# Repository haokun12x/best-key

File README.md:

# BK46 — 46 键正交 / 双直驱力反馈旋钮 / TMR + 机械轴共用 / 三模 / 无线充电

> **当前状态：外壳、主板、两块旋钮小板的制作文件齐全。三块板都已 100% 布通，KiCad DRC 零错误、零未连接（主板只剩 7 处元件占位框重叠的警告）。固件未写，电子部分整体未经打样验证，BOM 编号需核对。** 详见文末「完成度与待办」。

## 1. 方案总览

| 项目 | 方案 |
|---|---|
| 配列 | 4×12 正交网格，19.05 mm 间距；左上角、右上角两格换成旋钮，共 46 键 |
| 外形 | 237.2 × 84.8 × 19.8 mm（不含脚垫），四周只比键区多 4.3 mm，圆角 R4 |
| 轴体 | 每键同时有 Kailh 热插拔座（三脚/五脚机械轴）和一颗 SOT-23 线性磁传感器（磁轴） |
| 旋钮 | 2 个，1404 级无刷外转子电机直驱 + STSPIN233 驱动 + MT6701 磁编码器；带模拟量下压识别，咔哒与震动由电机模拟 |
| RGB | 每键一颗 WS2812B-2020，正面贴装在轴体灯位，整条灯带电源可关断 |
| 显示 | 0.91" 128×32 OLED（SSD1306，38×12 mm 成品模块），嵌在前壁中央 |
| 主控 | Raytac MDBT50Q-1MV2（nRF52840）：USB、蓝牙、2.4G（配 nRF52840 接收器） |
| 固件 | RMK（用 Vial 上位机改键/层/宏）或 ZMK；**不能刷 QMK / Vial-QMK**；预留 W25Q32 外置闪存。移植要点见 `docs/firmware.md` |
| 电源 | USB-C 或 Qi 5 V 接收模块 → BQ24075 充电与路径管理 → 304060 锂电（约 800 mAh）→ XC6206 3.3 V |
| 结构 | 底壳 + 上框两件式，定位板上下各 15 段 Poron 垫片夹持（gasket），底部 8 颗 M2×18 沉头螺丝 |
| 重量 | 尼龙打印外壳约 65 g（底壳 53 + 上框 12）；FR4 定位板约 24 g |

相对最初想法的改动：

- **旋钮**：真正的侧面表冠放不下任何现成直驱电机（除非凸出约 7 mm），最终按你的决定改为左右上角各一个立式旋钮。
- **下压**：不做有行程的按压机构（1u 空间里会晃）。电机座是小板上由 4 根 FR4 梁悬挂的小岛，按压时下沉几十微米，由背面轴心的磁传感器测出，输出模拟量，接到主板复用器空余的两路。没有采用 MT6701 自带的按钮功能，因为它需要零点几毫米的轴向行程。
- **显示屏**：按你的想法放在朝向用户的前壁。从上方看是斜视角，所以选了视角最宽的 OLED。
- **无线充电**：用成品 Qi 接收贴片（线圈 + 小板，输出 5 V），焊到主板 `QI5V`/`GND` 两个焊盘，不自己设计接收电路。

## 2. 叠层（Z 向，单位 mm，从底面算起）

图：`mech/out/drawings/00_stackup_section.svg`

| 高度 | 内容 |
|---|---|
| 0 – 1.6 | 底壳底板 |
| 1.6 – 7.2 | 腔体 5.6：电池 3.2、Qi 线圈约 1.3、热插拔座向下 1.85；旋钮小板 0.6 厚，垫高 0.4（2.0 – 2.6） |
| 7.2 – 8.8 | 主板 1.6（4 层） |
| 8.8 – 12.3 | 轴体下壳 / 夹心棉 3.5 |
| 11.1 | 底壳垫片台顶面 |
| 12.3 – 13.8 | 定位板 1.5（FR4 / PC / 铝均可） |
| 15.0 | 底壳与上框分界面，上框压边底面 |
| 15.0 – 19.8 | 上框 |
| 3.8 – 17.3 | 电机（座在 0.6 小板 + 1.2 垫片上） |
| 17.6 – 31.0 | 旋钮帽，直径 18.6 |

垫片：1.5 mm 厚 Poron 条，宽 1.5 mm，贴在定位板边缘正反两面，压缩到 1.2 mm。位置见 `05_gasket_positions_x2.dxf`。

## 3. 文件清单

```
index.html                  项目主页（逐层拆解展示，可直接用 GitHub Pages 从仓库根目录发布）
site/render/, render_previews.py   主页用的外壳线稿及生成脚本
mech/params.py              所有机械尺寸的唯一来源
mech/build_case.py          外壳 CAD 脚本（CadQuery），含干涉检查
mech/build_drawings.py      各层 DXF 图纸与叠层剖面图
mech/out/*.step, *.stl      底壳 tub、上框 bezel、定位板 plate、旋钮帽 knob_cap、旋钮芯 knob_core、电机垫片 motor_spacer
mech/out/bk46_assembly.step 总装（含 PCB、电池、线圈、电机、键帽包络等参考体）
mech/out/drawings/          00 叠层剖面  01 定位板  02 上框  03/04 底壳剖面与底孔  05 垫片位置  06 夹心棉  07 腔内布局
pcb/main/bk46_main.kicad_pcb / .kicad_pro   主板（4 层 1.6 mm）
pcb/main/unconnected.txt    主板连通状态（现为全部连通）
pcb/main/fab/               主板 Gerber、钻孔、贴片坐标、四层铜 SVG
pcb/main/bom_main.csv, keymap.json, netlist.json, drc.json
pcb/knob/L, pcb/knob/R      左、右旋钮小板（2 层 0.6 mm），各含 KiCad 工程和 fab/ 制板文件
pcb/knob/bom_knob.csv, ffc_pinmap.json
pcb/gen_main.py, gen_knob.py, router.py   板子的生成脚本和自写布线器
docs/firmware.md            固件移植说明：扫描、力反馈效果、下压识别、引脚
analysis/tmr_field.py, .svg 磁轴磁场仿真
tools/                      kpy.sh（KiCad 自带 Python）、drc.sh、freeroute.py（调用 Freerouting）、write_pro.py、sympins.py、
                            patch_route.py（拆线重布补线器）、clean_dangling.py（清悬空线）、finish_main.sh（主板收尾流程）
```

重新生成（主板约 2 分钟）：

```bash
.venv/bin/python mech/build_case.py
```
```bash
tools/kpy.sh pcb/gen_main.py
```
生成器自身会剩几处连不上的线，再用收尾流程补完（约 35 分钟，结果写到 `pcb/main_fin/`，确认后复制回 `pcb/main/`）：
```bash
tools/finish_main.sh pcb/main/bk46_main.kicad_pcb pcb/main_fin
```
```bash
tools/kpy.sh pcb/gen_knob.py
```
```bash
tools/kpy.sh tools/freeroute.py pcb/knob/L/bk46_knob_L_unrouted.kicad_pcb pcb/knob/L/bk46_knob_L.kicad_pcb 200 --zones=GND:F.Cu,GND:B.Cu
```

## 4. 电路架构

### 4.1 按键扫描（机械轴、磁轴、旋钮下压共用一条链路）

- 每键：传感器 OUT →10 kΩ→ `KEY` 节点 → CD74HC4067 的一路输入；热插拔座一脚接 `KEY`，另一脚接地。
- 装磁轴时 `KEY` 跟随传感器输出，读到模拟行程；装机械轴时按下把 `KEY` 拉到 0 V。固件校准时自动判定每个键是哪种轴。
- 没有二极管矩阵，天然全键无冲。3 颗 16 选 1 复用器共 48 路：46 个键 + 2 个旋钮下压。
- 传感器电源由 P-MOS 开关控制，空闲时低频间歇上电。
- 第 1、3 行轴体旋转 180°，使 PCB 前缘、后缘和中间各空出一条没有热插拔座的带状区域放元件。

### 4.2 主控引脚

| 功能 | 引脚 | 功能 | 引脚 |
|---|---|---|---|
| MUXA / MUXB / MUXC（ADC） | P0.29 / P0.31 / P0.30 | 电池电压 | P0.04 |
| 复用器 S0–S3 | P0.27, P0.06, P0.08, P1.09 | 传感器电源使能（低有效） | P1.12 |
| 左旋钮三相 PWM | P1.10, P1.11, P1.13 | 右旋钮三相 PWM | P0.13, P0.15, P0.17 |
| 编码器 CLK / DO（共用） | P0.22 / P0.24 | 编码器片选 左 / 右 | P1.15 / P0.20 |
| 旋钮电源使能（低有效） | P0.19 | 充电状态 | P0.03 |
| LED 数据 | P0.23 | LED 电源使能（高有效） | P1.14 |
| OLED SDA / SCL | P0.14 / P0.16 | 复位 | P0.18 |
| 外置闪存 CS / CLK / MOSI / MISO | P0.02 / P0.28 / P0.26 / P0.05 | | |

每个键的复用器通道和 LED 序号在 `pcb/main/keymap.json`。旋钮下压：左 = 复用器 A 通道 0，右 = 复用器 C 通道 15。

### 4.3 旋钮模块

- **小板**：0.6 mm 双层板。电机座是 13 mm 见方的小岛，四边各由一座 3 mm 宽的桥连到 2 mm 宽的 FR4 梁上，梁两端在四角用螺丝固定在底壳凸台上。估算刚度约 190 N/mm，4 N 按压下沉约 0.02 mm，未实测。
- **角度**：MT6701QT 在小岛正面轴心，对着粘在电机轴底的径向磁铁。
- **下压**：Z 向线性磁传感器（SOT-23）在小岛背面轴心，对着粘在底壳孔里的 Ø3×0.5 磁铁。
- **驱动**：STSPIN233 在小板尾部；使能脚固定上拉到旋钮电源，整路由主板的 P-MOS 开关控制。
- **排线**：14P 0.5 mm 同向 FFC，约 30 mm。主板连接器朝后壁出线，排线向下折 180° 插入正下方的小板连接器。引脚自西向东（左旋钮）：`VSYS ×3, GND ×3, K3V3, U, V, W, PRESS, CSN, CLK, DO`；右旋钮镜像。
- 电机三相线焊在小板的 M1–M3 焊盘。
- 力反馈效果、下压算法和低功耗策略见 `docs/firmware.md`。

## 5. 外购件

| 件 | 规格 | 数量 |
|---|---|---|
| 电机 | 1404 级无刷外转子，机身 ≤ Ø18.9 × 13.5，底部 4×M2（9×9 mm），T 型桨座（2×M2 间距 5 mm） | 2 |
| 径向充磁磁铁 | Ø4×2，粘在电机轴底端 | 2 |
| 轴向充磁磁铁 | Ø3×0.5，粘在底壳电机轴心孔内，与底面齐平 | 2 |
| OLED | 0.91" SSD1306 I2C 模块，PCB 38×12 | 1 |
| 电池 | 304060 锂聚合物，带保护板，JST-SH 2P（核对极性） | 1 |
| Qi 接收 | 5 V 成品接收贴片，线圈 ≤ 48×34 | 1 |
| FFC | 14P 0.5 mm 同向，30 mm | 2 |
| 螺丝 | M2×18 沉头（上框）×8；M2×4 盘头（电机，从小板背面拧入）×8；M2×3 自攻（小板固定）×10；M2×3（定位板铜柱）×20；M2×4（旋钮帽芯）×4 | |
| 铜柱 | M2×3.5 双通 | 10 |
| 垫片 | 1.5 mm Poron，裁 1.5 mm 宽 | 30 段 |
| 接收器 | nRF52840 USB Dongle（2.4G 模式用） | 1 |

主板元件见 `pcb/main/bom_main.csv`，小板见 `pcb/knob/bom_knob.csv`。立创编号是凭记忆填的，下单前必须逐个核对。

## 6. 装配顺序

1. 旋钮模块：电机垫片夹在小板和电机之间，4 颗 M2×4 从小板背面拧进电机底座；径向磁铁粘在轴底。
2. Ø3×0.5 磁铁粘进底壳轴心孔。把旋钮模块放到底壳凸台上，四角 4 颗、尾部 1 颗自攻螺丝固定。电机螺丝头落在底壳的让位孔里，不能碰到孔壁。
3. OLED 模块从上方滑入前壁口袋固定；电池、Qi 线圈贴在底板上（位置见 `07_floor_layout.dxf`）。
4. 主板与定位板用 10 根 3.5 mm 铜柱连接，装轴，定位板边缘正反贴垫片。
5. 接好两条排线、电池、Qi、OLED 四根线，USB 一端先斜插进后壁开口，再放平。
6. 盖上框，从底面拧 8 颗 M2×18。尼龙上框用自攻方式（底孔 Ø1.7），铝上框攻 M2 牙。
7. 旋钮芯用 2 颗 M2 拧在电机转子上，压上旋钮帽。

维修时拆 8 颗底部螺丝，上框可带着键帽直接提起，内胆随后取出。

## 7. 完成度与待办

### 已验证

- 外壳各零件与 PCB、电机、电池、线圈、显示模块、键帽包络之间的干涉检查全部为 0。
- 左、右旋钮小板：100% 布通，KiCad DRC 零违规、零未连接。
- 主板：100% 布通，KiCad DRC 零错误、零未连接、零悬空线、零孔距问题（间距规则 0.10 mm，最细线 0.15 mm，过孔 0.45/0.20 mm，属 4 层板常规工艺）。剩 7 处元件占位框重叠警告（两个 FFC 座与旁边阻容、C1/C2、C3 与 J1/U138），焊盘之间不冲突，贴片前看一眼即可。
- 所有 IC 的引脚定义取自 KiCad 官方符号库。

### 主板收尾时做的取舍

- 主控模块内圈焊盘之间只容得下 0.15 mm 线，所以补线统一用 0.15 mm；电源网络（VSYS、VBUS、VBAT、K3V3、VSENSE）重布时保持原线宽，VSYS 仍为 0.5 mm。
- 部分 +3V3 走线由 0.25 mm 换成了 0.15 mm（总电流约 0.2 A 以内，压降估计 30 mV 量级）。
- `CHG`、`SWDIO` 和一小段 +3V3 共约 13 mm 走在 In1 地平面上，地平面上因此有几条短缝，对这块板的信号影响很小。
- 删掉了 15 个与其他孔重叠或间距不足的 GND/VLED 过孔（地和 LED 电源有整层平面，连通性已由 DRC 复核）。

### 未完成

1. 没有原理图，网表以生成脚本和 `netlist.json` 为准。
2. 固件未写；`docs/firmware.md` 是移植说明，不是代码。
3. BOM 里的立创编号凭记忆填写，下单前逐个核对。

### 需要打样验证的风险

1. **按键传感器选型（最重要）**。传感器在轴心南侧 3.5 mm。`analysis/tmr_field.py` 的仿真结果：

   | 传感方式 | 释放 → 触底场强 | 是否单调 | 触底前 0.5 mm 的斜率 |
   |---|---|---|---|
   | 轴心正下方 Z 向（纯磁轴板的做法） | 9.6 → 58 mT | 是 | 33 mT/mm |
   | 偏 3.5 mm，Z 向（如 TMR2617S） | 5.4 → 10.3 mT | 否 | 0.4 mT/mm |
   | 偏 3.5 mm，面内径向 | 4.1 → 19.5 mT | 是 | 8.1 mT/mm |

   应选**面内感应**的线性 TMR，敏感轴指向轴心。BOM 里暂填的 TMR2617S 是 Z 向的，在这个位置触底前约 0.7 mm 分辨不出行程。我没能确认具体的面内型号，磁铁尺寸也是假设值，建议先做 2×2 小板验证；若所选传感器敏感轴方向不同，封装要转 90°。
2. **旋钮下压灵敏度**。梁的刚度和磁场梯度都是估算，按 4 N 约 1 mT 的信号量级设计；实际偏小可把小板换成 0.4 mm 或把梁铣窄，偏大则加厚。电机磁钢对下压传感器的串扰未评估。
3. **MT6701 的 MODE 脚**按"接地 = SSI/I2C"连接，需对照手册确认。
4. **力反馈强度**约 5 mN·m 是按电机参数估算的。电机相电阻很低，固件必须限流。
5. **左旋钮 PWM 用了 P1.10/P1.11/P1.13**，属于芯片的低频引脚，出力时可能影响蓝牙灵敏度。
6. **电机尺寸**因品牌而异，`params.py` 里 `MOTOR_*` 要按实物改。
7. **RGB 供电**直接用电池电压，电量低时蓝绿光偏暗；固件要限制总电流。
8. **无线充电**的交变磁场和带磁吸的充电座会干扰磁传感器。
9. **天线**在板子中部，周围是铺铜和金属轴座，蓝牙距离会打折扣。
10. **显示模块**的显示区偏移因厂家而异，`DISP_WIN_DX` 要按实物量。
11. **正贴 2020 灯珠**能否放进轴体灯槽取决于轴体，放不下可换 1.5×1.5 的 SK6805-EC15。
12. 0.6 mm 的旋钮小板较软，贴片时需要托板。

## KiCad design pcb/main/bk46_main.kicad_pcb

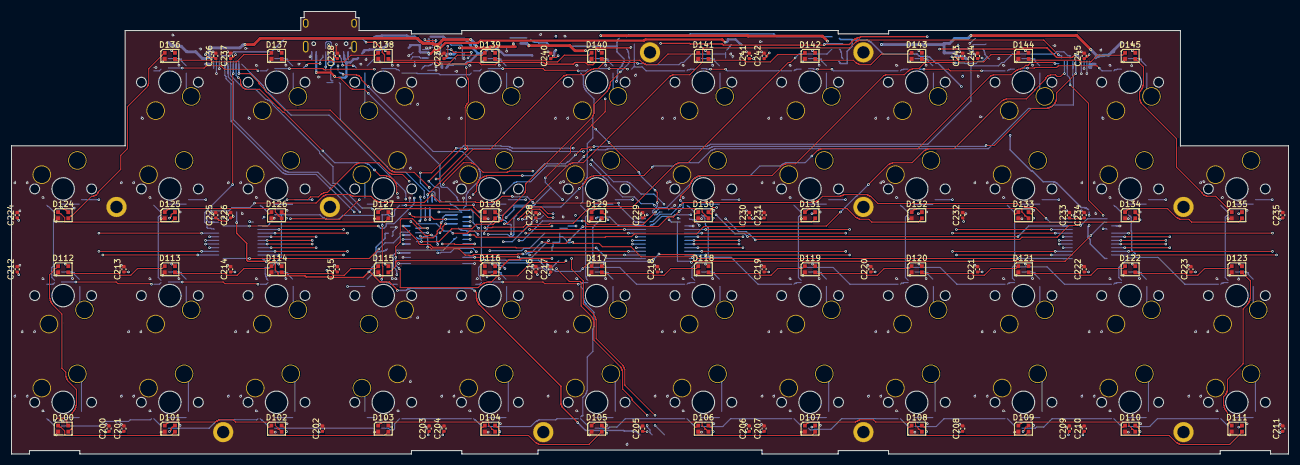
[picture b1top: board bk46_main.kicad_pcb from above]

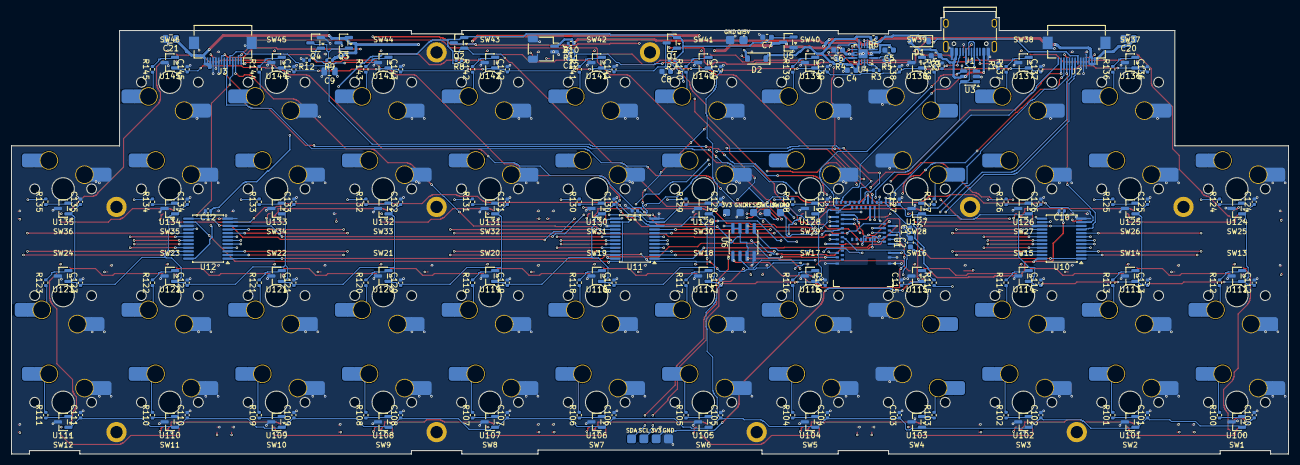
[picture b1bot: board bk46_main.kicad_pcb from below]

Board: 4 copper layers, 228.0 x 79.0 mm, 341 parts (183 on the bottom side), 190 nets.

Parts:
C1, C10, C11, C12, C12#2, C200, C201, C202, C203, C204, C205, C206, C207, C208, C209, C210, C211, C212, C213, C214, C215, C216, C217, C218, C219, C220, C221, C222, C223, C224, C225, C226, C228, C229, C230, C231, C232, C233, C234, C235, C236, C237, C238, C239, C240, C241, C242, C243, C244, C245: 100n; C_0402_1005Metric
C2, C3, C5, C6: 4u7; C_0603_1608Metric
C4, C7, C8: 1u; C_0603_1608Metric
C9: 10u; C_0805_2012Metric
C20, C21: 22u; C_0805_2012Metric
C100, C101, C102, C103, C104, C105, C106, C107, C108, C109, C110, C111, C112, C113, C114, C115, C116, C117, C118, C119, C120, C121, C122, C123, C124, C125, C126, C127, C128, C129, C130, C131, C132, C133, C134, C135, C136, C137, C138, C139, C140, C141, C142, C143, C144, C145: 22n; C_0402_1005Metric
D1, D2: B5819W; D_SOD-123
D100, D101, D102, D103, D104, D105, D106, D107, D108, D109, D110, D111, D112, D113, D114, D115, D116, D117, D118, D119, D120, D121, D122, D123, D124, D125, D126, D127, D128, D129, D130, D131, D132, D133, D134, D135, D136, D137, D138, D139, D140, D141, D142, D143, D144, D145: WS2812B-2020; LED_WS2812B-2020_PLCC4_2.0x2.0mm
H1, H2, H3, H4, H5, H6, H7, H8, H9, H10: M2 standoff 3.5mm
J1: USB-C 16P; USB_C_Receptacle_HRO_TYPE-C-31-M-12
J2, J3: FFC 14P 0.5mm; Hirose_FH12-14S-0.5SH_1x14-1MP_P0.50mm_Horizontal
J4: BAT (JST-SH 2P); JST_SH_SM02B-SRSS-TB_1x02-1MP_P1.00mm_Horizontal
Q1, Q2, Q3: AO3401A; SOT-23
Q4: 2N7002; SOT-23
R1, R2: 5k1; R_0402_1005Metric
R3: 2k2; R_0402_1005Metric
R4: 1k5; R_0402_1005Metric
R5, R6, R100, R101, R102, R103, R104, R105, R106, R107, R108, R109, R110, R111, R112, R113, R114, R115, R116, R117, R118, R119, R120, R121, R122, R123, R124, R125, R126, R127, R128, R129, R130, R131, R132, R133, R134, R135, R136, R137, R138, R139, R140, R141, R142, R143, R144, R145: 10k; R_0402_1005Metric
R7, R8, R9, R12: 100k; R_0402_1005Metric
R10, R11: 1M; R_0402_1005Metric
SW1, SW2, SW3, SW4, SW5, SW6, SW7, SW8, SW9, SW10, SW11, SW12, SW13, SW14, SW15, SW16, SW17, SW18, SW19, SW20, SW21, SW22, SW23, SW24, SW25, SW26, SW27, SW28, SW29, SW30, SW31, SW32, SW33, SW34, SW35, SW36, SW37, SW38, SW39, SW40, SW41, SW42, SW43, SW44, SW45, SW46: MX_HS_TMR
TP1: QI5V
TP2, TP10, TP23: GND
TP11, TP24: +3V3
TP12: SCL
TP13: SDA
TP20: SWDIO
TP21: SWCLK
TP22: RESET
U1: MDBT50Q-1MV2; Raytac_MDBT50Q
U3: USBLC6-2SC6; SOT-23-6
U4: BQ24075RGT; VQFN-16-1EP_3x3mm_P0.5mm_EP1.6x1.6mm
U5: XC6206P332MR; SOT-23
U6: W25Q32JVSSIQ (optional); SOIC-8_3.9x4.9mm_P1.27mm
U10, U11, U12: CD74HC4067SM96; SSOP-24_5.3x8.2mm_P0.65mm
U100, U101, U102, U103, U104, U105, U106, U107, U108, U109, U110, U111, U112, U113, U114, U115, U116, U117, U118, U119, U120, U121, U122, U123, U124, U125, U126, U127, U128, U129, U130, U131, U132, U133, U134, U135, U136, U137, U138, U139, U140, U141, U142, U143, U144, U145: TMR2617S; SOT-23

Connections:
+3V3: C1.1, C2.1, C7.1, C10.1, C11.1, C12#2.1, Q1.2, Q2.2, R7.1, R8.1, TP11.1, TP24.1, U1.28, U1.30, U5.2, U6.3, U6.7, U6.8, U10.24, U11.24, U12.24
CC1: J1.A5, R1.1
CC2: J1.B5, R2.1
CHG: U1.9, U4.9
EN1: R6.1, U4.6
ENC_CLK: J2.13, J3.2, U1.46
ENC_CSN1: J2.12, U1.8
ENC_CSN2: J3.3, U1.44
ENC_DO: J2.14, J3.1, U1.48
FL_CLK: U1.13, U6.6
FL_CS: U1.11, U6.1
FL_MISO: U1.21, U6.2
FL_MOSI: U1.19, U6.5
GND: C1.2, C2.2, C3.2, C4.2, C5.2, C6.2, C7.2, C8.2, C9.2, C10.2, C11.2, C12.2, C12#2.2, C20.2, C21.2, C100.2, C101.2, C102.2, C103.2, C104.2, C105.2, C106.2, C107.2, C108.2, C109.2, C110.2, C111.2, C112.2, C113.2, C114.2, C115.2, C116.2, C117.2, C118.2, C119.2, C120.2, C121.2, C122.2, C123.2, C124.2, C125.2, C126.2, C127.2, C128.2, C129.2, C130.2, C131.2, C132.2, C133.2, C134.2, C135.2, C136.2, C137.2, C138.2, C139.2, C140.2, C141.2, C142.2, C143.2, C144.2, C145.2, C200.2, C201.2, C202.2, C203.2, C204.2, C205.2, C206.2, C207.2, C208.2, C209.2, C210.2, C211.2, C212.2, C213.2, C214.2, C215.2, C216.2, C217.2, C218.2, C219.2, C220.2, C221.2, C222.2, C223.2, C224.2, C225.2, C226.2, C228.2, C229.2, C230.2, C231.2, C232.2, C233.2, C234.2, C235.2, C236.2, C237.2, C238.2, C239.2, C240.2, C241.2, C242.2, C243.2, C244.2, C245.2, D100.2, D101.2, D102.2, D103.2, D104.2, D105.2, D106.2, D107.2, D108.2, D109.2, D110.2, D111.2, D112.2, D113.2, D114.2, D115.2, D116.2, D117.2, D118.2, D119.2, D120.2, D121.2, D122.2, D123.2, D124.2, D125.2, D126.2, D127.2, D128.2, D129.2, D130.2, D131.2, D132.2, D133.2, D134.2, D135.2, D136.2, D137.2, D138.2, D139.2, D140.2, D141.2, D142.2, D143.2, D144.2, D145.2, H1.1, H2.1, H3.1, H4.1, H5.1, H6.1, H7.1, H8.1, H9.1, H10.1, J1.A1, J1.A12, J1.B1, J1.B12, J1.SH, J2.4, J2.5, J2.6, J2.MP, J3.9, J3.10, J3.11, J3.MP, J4.2, J4.MP, Q4.2, R1.2, R2.2, R3.2, R4.2, R5.2, R11.2, R12.2, SW1.1, SW2.1, SW3.1, SW4.2, SW5.1, SW6.1, SW7.1, SW8.1, SW9.1, SW10.1, SW11.1, SW12.1, SW13.2, SW14.2, SW15.2, SW16.1, SW17.2, SW18.2, SW19.2, SW20.2, SW21.2, SW22.2, SW23.2, SW24.2, SW25.1, SW26.1, SW27.1, SW28.2, SW29.1, SW30.1, SW31.1, SW32.1, SW33.1, SW34.1, SW35.1, SW36.1, SW37.2, SW38.2, SW39.1, SW40.2, SW41.2, SW42.2, SW43.2, SW44.2, SW45.2, SW46.2, TP2.1, TP10.1, TP23.1, U1.1, U1.2, U1.15, U1.33, U1.55, U3.2, U4.4, U4.5, U4.8, U4.15, U4.17, U5.1, U6.4, U10.12, U10.15, U11.12, U11.15, U12.12, U12.15, U100.3, U101.3, U102.3, U103.3, U104.3, U105.3, U106.3, U107.3, U108.3, U109.3, U110.3, U111.3, U112.3, U113.3, U114.3, U115.3, U116.3, U117.3, U118.3, U119.3, U120.3, U121.3, U122.3, U123.3, U124.3, U125.3, U126.3, U127.3, U128.3, U129.3, U130.3, U131.3, U132.3, U133.3, U134.3, U135.3, U136.3, U137.3, U138.3, U139.3, U140.3, U141.3, U142.3, U143.3, U144.3, U145.3
ILIM: R4.1, U4.12
ISET: R3.1, U4.16
K1U: J2.8, U1.3
K1V: J2.9, U1.4
K1W: J2.10, U1.6
K2U: J3.7, U1.37
K2V: J3.6, U1.39
K2W: J3.5, U1.41
K3V3: J2.7, J3.8, Q2.3
KEY_0_0: R100.2, SW1.2, U10.2
KEY_0_1: R112.1, SW13.1, U10.3
KEY_0_2: R124.2, SW25.2, U10.8
KEY_1_0: R101.2, SW2.2, U10.4
KEY_1_1: R113.1, SW14.1, U10.5
KEY_1_2: R125.2, SW26.2, U10.6
KEY_1_3: R136.1, SW37.1, U10.7
KEY_2_0: R102.2, SW3.2, U10.21
KEY_2_1: R114.1, SW15.1, U10.20
KEY_2_2: R126.2, SW27.2, U10.19
KEY_2_3: R137.1, SW38.1, U10.18
KEY_3_0: R103.2, SW4.1, U10.23
KEY_3_1: R115.1, SW16.2, U10.22
KEY_3_2: R127.2, SW28.1, U10.17
KEY_3_3: R138.1, SW39.2, U10.16
KEY_4_0: R104.2, SW5.2, U11.2
KEY_4_1: R116.1, SW17.1, U11.3
KEY_4_2: R128.2, SW29.2, U11.8
KEY_4_3: R139.1, SW40.1, U11.9
KEY_5_0: R105.2, SW6.2, U11.4
KEY_5_1: R117.1, SW18.1, U11.5
KEY_5_2: R129.2, SW30.2, U11.6
KEY_5_3: R140.1, SW41.1, U11.7
KEY_6_0: R106.2, SW7.2, U11.21
KEY_6_1: R118.1, SW19.1, U11.20
KEY_6_2: R130.2, SW31.2, U11.19
KEY_6_3: R141.1, SW42.1, U11.18
KEY_7_0: R107.2, SW8.2, U11.23
KEY_7_1: R119.1, SW20.1, U11.22
KEY_7_2: R131.2, SW32.2, U11.17
KEY_7_3: R142.1, SW43.1, U11.16
KEY_8_0: R108.2, SW9.2, U12.2
KEY_8_1: R120.1, SW21.1, U12.3
KEY_8_2: R132.2, SW33.2, U12.8
KEY_8_3: R143.1, SW44.1, U12.9
KEY_9_0: R109.2, SW10.2, U12.4
KEY_9_1: R121.1, SW22.1, U12.5
KEY_9_2: R133.2, SW34.2, U12.6
KEY_9_3: R144.1, SW45.1, U12.7
KEY_10_0: R110.2, SW11.2, U12.21
KEY_10_1: R122.1, SW23.1, U12.20
KEY_10_2: R134.2, SW35.2, U12.19
KEY_10_3: R145.1, SW46.1, U12.18
KEY_11_0: R111.2, SW12.2, U12.23
KEY_11_1: R123.1, SW24.1, U12.22
KEY_11_2: R135.2, SW36.2, U12.17
KNOB_PWR_EN: Q2.1, R8.2, U1.42
LD1: D115.3, D116.1
LD2: D114.3, D115.1
LD3: D113.3, D114.1
LD4: D112.3, D113.1
LD5: D100.3, D112.1
LD6: D100.1, D101.3
LD7: D101.1, D102.3
LD8: D102.1, D103.3
LD9: D103.1, D104.3
LD10: D104.1, D105.3
LD11: D105.1, D106.3
LD12: D106.1, D107.3
LD13: D107.1, D108.3
LD14: D108.1, D109.3
LD15: D109.1, D110.3
LD16: D110.1, D111.3
LD17: D111.1, D123.3
LD18: D122.3, D123.1
LD19: D121.3, D122.1
LD20: D120.3, D121.1
LD21: D119.3, D120.1
LD22: D118.3, D119.1
LD23: D117.3, D118.1
LD24: D117.1, D129.3
LD25: D129.1, D130.3
LD26: D130.1, D131.3
LD27: D131.1, D132.3
LD28: D132.1, D133.3
LD29: D133.1, D134.3
LD30: D134.1, D135.3
LD31: D135.1, D145.3
LD32: D144.3, D145.1
LD33: D143.3, D144.1
LD34: D142.3, D143.1
LD35: D141.3, D142.1
LD36: D140.3, D141.1
LD37: D139.3, D140.1
LD38: D138.3, D139.1
LD39: D137.3, D138.1
LD40: D136.3, D137.1
LD41: D124.3, D136.1
LD42: D124.1, D125.3
LD43: D125.1, D126.3
LD44: D126.1, D127.3
LD45: D127.1, D128.3
LED_DIN: D116.3, U1.45
LED_EN: Q4.1, R12.1, U1.7
LED_G: Q3.1, Q4.3, R9.2
MUXA: U1.10, U10.1
MUXB: U1.12, U11.1
MUXC: U1.14, U12.1
PRESS1: J2.11, U10.9
PRESS2: J3.4, U12.16
QI5V: D2.2, TP1.1
RESET: TP22.1, U1.40
S0: U1.16, U10.10, U11.10, U12.10
S1: U1.22, U10.11, U11.11, U12.11
S2: U1.24, U10.14, U11.14, U12.14
S3: U1.26, U10.13, U11.13, U12.13
SCL: TP12.1, U1.38
SDA: TP13.1, U1.36
SENSE_EN: Q1.1, R7.2, U1.5
SO_0_0: R100.1, U100.2
SO_0_1: R112.2, U112.2
SO_0_2: R124.1, U124.2
SO_1_0: R101.1, U101.2
SO_1_1: R113.2, U113.2
SO_1_2: R125.1, U125.2
SO_1_3: R136.2, U136.2
SO_2_0: R102.1, U102.2
SO_2_1: R114.2, U114.2
SO_2_2: R126.1, U126.2
SO_2_3: R137.2, U137.2
SO_3_0: R103.1, U103.2
SO_3_1: R115.2, U115.2
SO_3_2: R127.1, U127.2
SO_3_3: R138.2, U138.2
SO_4_0: R104.1, U104.2
SO_4_1: R116.2, U116.2
SO_4_2: R128.1, U128.2
SO_4_3: R139.2, U139.2
SO_5_0: R105.1, U105.2
SO_5_1: R117.2, U117.2
SO_5_2: R129.1, U129.2
SO_5_3: R140.2, U140.2
SO_6_0: R106.1, U106.2
SO_6_1: R118.2, U118.2
SO_6_2: R130.1, U130.2
SO_6_3: R141.2, U141.2
SO_7_0: R107.1, U107.2
SO_7_1: R119.2, U119.2
SO_7_2: R131.1, U131.2
SO_7_3: R142.2, U142.2
SO_8_0: R108.1, U108.2
SO_8_1: R120.2, U120.2
SO_8_2: R132.1, U132.2
SO_8_3: R143.2, U143.2
SO_9_0: R109.1, U109.2
SO_9_1: R121.2, U121.2
SO_9_2: R133.1, U133.2
SO_9_3: R144.2, U144.2
SO_10_0: R110.1, U110.2
SO_10_1: R122.2, U122.2
SO_10_2: R134.1, U134.2
SO_10_3: R145.2, U145.2
SO_11_0: R111.1, U111.2
SO_11_1: R123.2, U123.2
SO_11_2: R135.1, U135.2
SWCLK: TP21.1, U1.53
SWDIO: TP20.1, U1.51
TS: R5.1, U4.1
USB_DM: J1.A7, J1.B7, U1.34, U3.3, U3.4
USB_DP: J1.A6, J1.B6, U1.35, U3.1, U3.6
VBAT: C5.1, J4.1, R10.1, U4.2, U4.3
VBAT_SNS: C12.1, R10.2, R11.1, U1.20
VBUS: C3.1, D1.2, J1.A4, J1.A9, J1.B4, J1.B9, U1.32, U3.5
VIN: C4.1, D1.1, D2.1, R6.2, U4.13
VLED: C9.1, C200.1, C201.1, C202.1, C203.1, C204.1, C205.1, C206.1, C207.1, C208.1, C209.1, C210.1, C211.1, C212.1, C213.1, C214.1, C215.1, C216.1, C217.1, C218.1, C219.1, C220.1, C221.1, C222.1, C223.1, C224.1, C225.1, C226.1, C228.1, C229.1, C230.1, C231.1, C232.1, C233.1, C234.1, C235.1, C236.1, C237.1, C238.1, C239.1, C240.1, C241.1, C242.1, C243.1, C244.1, C245.1, D100.4, D101.4, D102.4, D103.4, D104.4, D105.4, D106.4, D107.4, D108.4, D109.4, D110.4, D111.4, D112.4, D113.4, D114.4, D115.4, D116.4, D117.4, D118.4, D119.4, D120.4, D121.4, D122.4, D123.4, D124.4, D125.4, D126.4, D127.4, D128.4, D129.4, D130.4, D131.4, D132.4, D133.4, D134.4, D135.4, D136.4, D137.4, D138.4, D139.4, D140.4, D141.4, D142.4, D143.4, D144.4, D145.4, Q3.3
VSENSE: C8.1, C100.1, C101.1, C102.1, C103.1, C104.1, C105.1, C106.1, C107.1, C108.1, C109.1, C110.1, C111.1, C112.1, C113.1, C114.1, C115.1, C116.1, C117.1, C118.1, C119.1, C120.1, C121.1, C122.1, C123.1, C124.1, C125.1, C126.1, C127.1, C128.1, C129.1, C130.1, C131.1, C132.1, C133.1, C134.1, C135.1, C136.1, C137.1, C138.1, C139.1, C140.1, C141.1, C142.1, C143.1, C144.1, C145.1, Q1.3, U100.1, U101.1, U102.1, U103.1, U104.1, U105.1, U106.1, U107.1, U108.1, U109.1, U110.1, U111.1, U112.1, U113.1, U114.1, U115.1, U116.1, U117.1, U118.1, U119.1, U120.1, U121.1, U122.1, U123.1, U124.1, U125.1, U126.1, U127.1, U128.1, U129.1, U130.1, U131.1, U132.1, U133.1, U134.1, U135.1, U136.1, U137.1, U138.1, U139.1, U140.1, U141.1, U142.1, U143.1, U144.1, U145.1
VSYS: C6.1, C20.1, C21.1, J2.1, J2.2, J2.3, J3.12, J3.13, J3.14, Q3.2, R9.1, U4.10, U4.11, U5.3

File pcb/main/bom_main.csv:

Qty,Value,Footprint,Part / LCSC (verify before ordering),Refs
50,100n,Capacitor_SMD:C_0402_1005Metric,C1525,C200 ... C12
48,10k,Resistor_SMD:R_0402_1005Metric,C25744,R100 ... R6
46,TMR2617S,Package_TO_SOT_SMD:SOT-23,TMR2617S (MDT),U100 ... U145
46,22n,Capacitor_SMD:C_0402_1005Metric,C1532,C100 ... C145
46,WS2812B-2020,LED_SMD:LED_WS2812B-2020_PLCC4_2.0x2.0mm,C965555,D100 ... D145
4,4u7,Capacitor_SMD:C_0603_1608Metric,C19666,C2 C3 C5 C6
4,100k,Resistor_SMD:R_0402_1005Metric,C25741,R7 R9 R12 R8
3,CD74HC4067SM96,Package_SO:SSOP-24_5.3x8.2mm_P0.65mm,C98457,U10 U11 U12
3,1u,Capacitor_SMD:C_0603_1608Metric,C15849,C4 C7 C8
3,AO3401A,Package_TO_SOT_SMD:SOT-23,C15127,Q1 Q3 Q2
2,5k1,Resistor_SMD:R_0402_1005Metric,C25905,R1 R2
2,B5819W,Diode_SMD:D_SOD-123,C8598,D1 D2
2,1M,Resistor_SMD:R_0402_1005Metric,C26083,R10 R11
2,FFC 14P 0.5mm,Connector_FFC-FPC:Hirose_FH12-14S-0.5SH_1x14-1MP_P0.50mm_Horizontal,C11084,J2 J3
2,22u,Capacitor_SMD:C_0805_2012Metric,C45783,C20 C21
1,MDBT50Q-1MV2,RF_Module:Raytac_MDBT50Q,C5118826,U1
1,W25Q32JVSSIQ (optional),Package_SO:SOIC-8_3.9x4.9mm_P1.27mm,C179171,U6
1,USB-C 16P,Connector_USB:USB_C_Receptacle_HRO_TYPE-C-31-M-12,C165948,J1
1,USBLC6-2SC6,Package_TO_SOT_SMD:SOT-23-6,C7519,U3
1,BQ24075RGT,Package_DFN_QFN:VQFN-16-1EP_3x3mm_P0.5mm_EP1.6x1.6mm,C15220,U4
1,2k2,Resistor_SMD:R_0402_1005Metric,C25879,R3
1,1k5,Resistor_SMD:R_0402_1005Metric,C25867,R4
1,XC6206P332MR,Package_TO_SOT_SMD:SOT-23,C5446,U5
1,pad QI5V,solder pad 1.5mm,-,TP1
1,pad GND,solder pad 1.5mm,-,TP2
1,2N7002,Package_TO_SOT_SMD:SOT-23,C8545,Q4
1,10u,Capacitor_SMD:C_0805_2012Metric,C15850,C9
1,BAT (JST-SH 2P),Connector_JST:JST_SH_SM02B-SRSS-TB_1x02-1MP_P1.00mm_Horizontal,C160402,J4
1,pad GND,solder pad 1.6mm,-,TP10
1,pad +3V3,solder pad 1.6mm,-,TP11
1,pad SCL,solder pad 1.6mm,-,TP12
1,pad SDA,solder pad 1.6mm,-,TP13
1,pad SWDIO,solder pad 1.3mm,-,TP20
1,pad SWCLK,solder pad 1.3mm,-,TP21
1,pad RESET,solder pad 1.3mm,-,TP22
1,pad GND,solder pad 1.3mm,-,TP23
1,pad +3V3,solder pad 1.3mm,-,TP24
46,Kailh hot-swap socket CPG151101S11,in key footprint SW1..SW46,C2803348,SW1 ... SW46
